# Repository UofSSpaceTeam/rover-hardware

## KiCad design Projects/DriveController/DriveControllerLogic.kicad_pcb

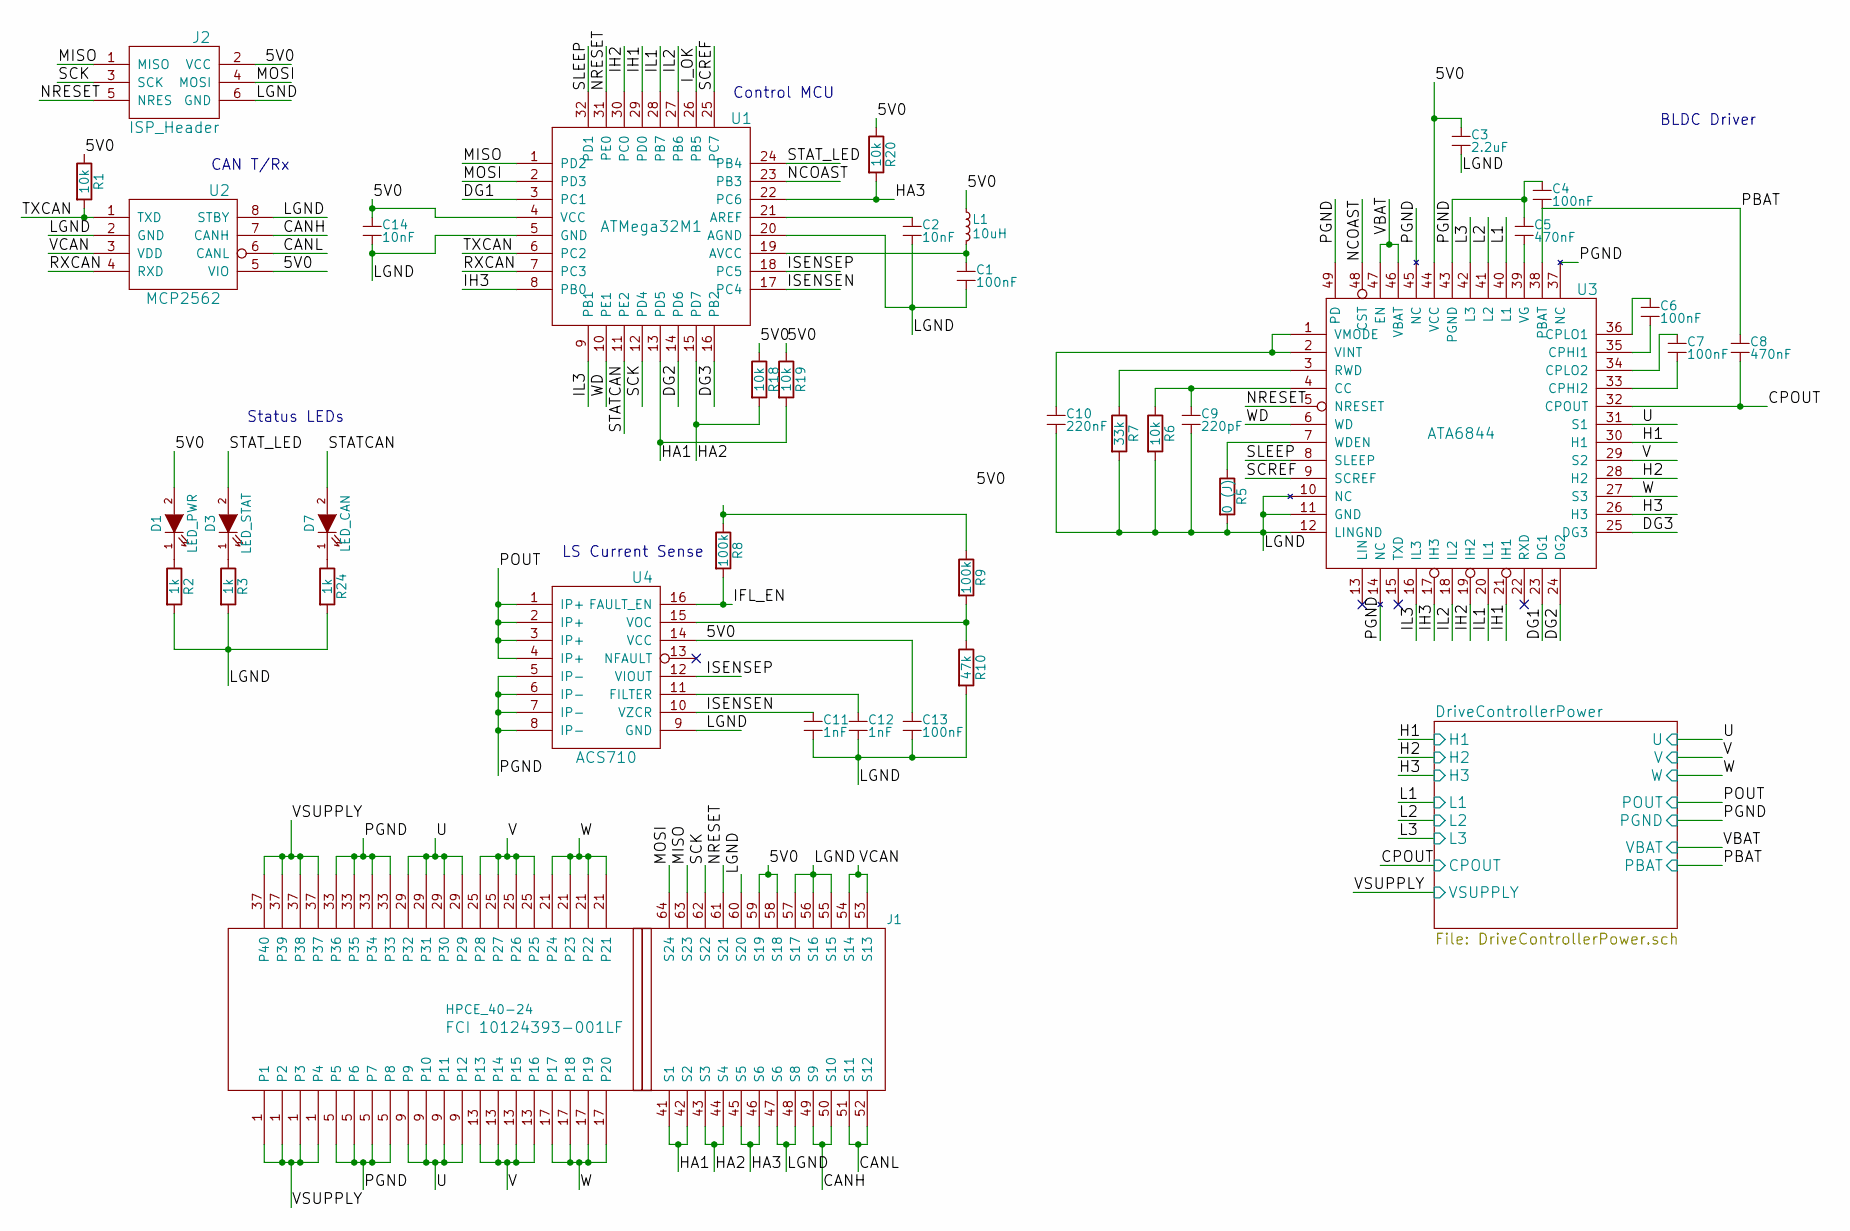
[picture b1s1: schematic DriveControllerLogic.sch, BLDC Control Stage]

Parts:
C1, C4, C6, C7, C13: 100nF; C_0805
C2, C14: 10nF; C_0805
C3: 2.2uF; C_0805
C5, C8: 470nF; C_0805
C9: 220pF; C_0805
C10: 220nF; C_0805
C11, C12: 1nF; C_0805
D1: LED_PWR; LED-0805
D3: LED_STAT; LED-0805
D7: LED_CAN; LED-0805
J1: HPCE_40-24; HPCE-40-24; Part FCI 10124393-001LF
J2: ISP_Header; Pin_Header_Straight_2x03
L1: 10uH; C_0805
R1, R6, R18, R19, R20: 10k; R_0805
R2, R3, R24: 1k; R_0805
R5: 0 (J); R_0805
R7: 33k; R_0805
R8, R9: 100k; R_0805
R10: 47k; R_0805
U1: ATMega32M1; TQFP-32_7x7mm_Pitch0.8mm
U2: MCP2562; SOIC-8_3.9x4.9mm_Pitch1.27mm
U3: ATA6844; QFN-48-1EP_7x7mm_Pitch0.5mm
U4: ACS710; SOIC-16_7.5x10.3mm_Pitch1.27mm

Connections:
/5V0: C3.1, C13.1, C14.1, D1.2 (A), J1.58 (S18), J1.59 (S19), J2.2 (VCC), L1.1, R1.1, R18.1, R19.1, R20.1, U1.4 (VCC), U2.5 (VIO), U3.44 (VCC), U4.14 (VCC)
/CANH: J1.49 (S9), J1.50 (S10), U2.7 (CANH)
/CANL: J1.51 (S11), J1.52 (S12), U2.6 (CANL)
/DG1: U1.3 (PC1), U3.23 (DG1)
/DG2: U1.14 (PD6), U3.24 (DG2)
/DG3: U1.16 (PB2), U3.25 (DG3)
/DriveControllerPower/CPOUT: C8.2, U3.32 (CPOUT); also elsewhere on the board
/DriveControllerPower/H1: U3.30 (H1); also elsewhere on the board
/DriveControllerPower/H2: U3.28 (H2); also elsewhere on the board
/DriveControllerPower/H3: U3.26 (H3); also elsewhere on the board
/DriveControllerPower/L1: U3.40 (L1); also elsewhere on the board
/DriveControllerPower/L2: U3.41 (L2); also elsewhere on the board
/DriveControllerPower/L3: U3.42 (L3); also elsewhere on the board
/DriveControllerPower/PBAT: C4.2, C8.1, U3.38 (PBAT); also elsewhere on the board
/DriveControllerPower/PGND: C4.1, C5.1, J1.5, J1.33, U3.14 (NC), U3.37 (NC), U3.43 (PGND), U3.45 (NC), U3.49 (PD), U4.5 (IP-), U4.6 (IP-), U4.7 (IP-), U4.8 (IP-); also elsewhere on the board
/DriveControllerPower/POUT: U4.1 (IP+), U4.2 (IP+), U4.3 (IP+), U4.4 (IP+); also elsewhere on the board
/DriveControllerPower/U: J1.9 (P10), J1.29, U3.31 (S1); also elsewhere on the board
/DriveControllerPower/V: J1.13, J1.25, U3.29 (S2); also elsewhere on the board
/DriveControllerPower/VBAT: U3.46 (VBAT), U3.47 (EN); also elsewhere on the board
/DriveControllerPower/VSUPPLY: J1.1, J1.37; also elsewhere on the board
/DriveControllerPower/W: J1.17, J1.21, U3.27 (S3); also elsewhere on the board
/HA1: J1.41 (S1), J1.42 (S2), R19.2, U1.13 (PD5)
/HA2: J1.43 (S3), J1.44 (S4), R18.2, U1.15 (PD7)
/HA3: J1.45 (S5), J1.46 (S6), R20.2, U1.22 (PC6)
/IFL_EN: R8.2, U4.16 (FAULT_EN)
/IH1: U1.29 (PD0), U3.21 (IH1)
/IH2: U1.30 (PC0), U3.19 (IH2)
/IH3: U1.8 (PB0), U3.17 (IH3)
/IL1: U1.28 (PB7), U3.20 (IL1)
/IL2: U1.27 (PB6), U3.18 (IL2)
/IL3: U1.9 (PB1), U3.16 (IL3)
/ISENSEN: C11.1, U1.17 (PC4), U4.10 (VZCR)
/ISENSEP: U1.18 (PC5), U4.12 (VIOUT)
/LGND: C1.2, C2.2, C3.2, C9.2, C10.2, C11.2, C12.2, C13.2, C14.2, J1.47 (S6), J1.48 (S8), J1.55 (S15), J1.56 (S16), J1.57 (S17), J1.60 (S20), J2.6 (GND), R2.2, R3.2, R5.2, R6.2, R7.2, R10.2, R24.2, U1.5 (GND), U1.20 (AGND), U2.2 (GND), U2.8 (STBY), U3.10 (NC), U3.11 (GND), U3.12 (LINGND), U4.9 (GND)
/MISO: J1.63 (S23), J2.1 (MISO), U1.1 (PD2)
/MOSI: J1.64 (S24), J2.4 (MOSI), U1.2 (PD3)
/NCOAST: U1.23 (PB3), U3.48 (CST)
/NRESET: J1.61 (S21), J2.5 (NRES), U1.31 (PE0), U3.5 (NRESET)
/RXCAN: U1.7 (PC3), U2.4 (RXD)
/SCK: J1.62 (S22), J2.3 (SCK), U1.12 (PD4)
/SCREF: U1.25 (PC7), U3.9 (SCREF)
/SLEEP: U1.32 (PD1), U3.8 (SLEEP)
/STATCAN: D7.2 (A), U1.11 (PE2)
/STAT_LED: D3.2 (A), U1.24 (PB4)
/TXCAN: R1.2, U1.6 (PC2), U2.1 (TXD)
/VCAN: J1.53 (S13), J1.54 (S14), U2.3 (VDD)
/WD: U1.10 (PE1), U3.6 (WD)
unnamed: C1.1, L1.2, U1.19 (AVCC)
unnamed: C2.1, U1.21 (AREF)
unnamed: C5.2, U3.39 (VG)
unnamed: C6.1, U3.36 (CPLO1)
unnamed: C6.2, U3.35 (CPHI1)
unnamed: C7.1, U3.34 (CPLO2)
unnamed: C7.2, U3.33 (CPHI2)
unnamed: C9.1, R6.1, U3.4 (CC)
unnamed: C10.1, U3.1 (VMODE), U3.2 (VINT)
unnamed: C12.1, U4.11 (FILTER)
unnamed: D1.1 (K), R2.1
unnamed: D3.1 (K), R3.1
unnamed: D7.1 (K), R24.1
unnamed: R5.1, U3.7 (WDEN)
unnamed: R7.1, U3.3 (RWD)
unnamed: R8.1, R9.1
unnamed: R9.2, R10.1, U4.15 (VOC)

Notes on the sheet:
CAN T/Rx
Control MCU
BLDC Driver
LS Current Sense
Status LEDs

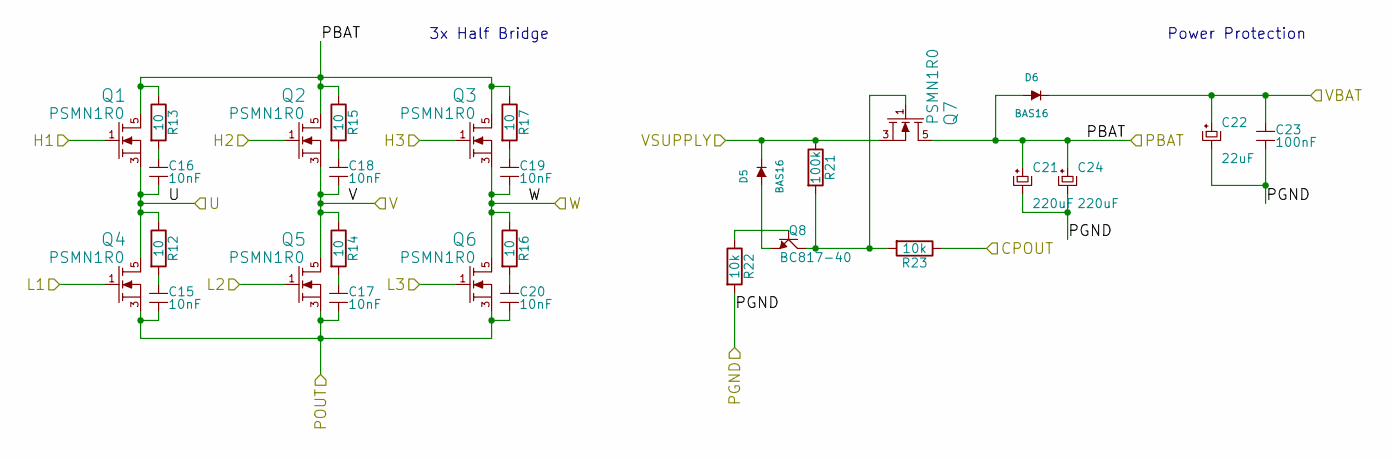
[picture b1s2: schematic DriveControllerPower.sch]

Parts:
C15, C16, C17, C18, C19, C20: 10nF; C_0805
C21, C24: 220uF; c_elec_10x10
C22: 22uF; c_elec_6.3x5.7
C23: 100nF; C_0805
D5, D6: BAS16; SOT-23
Q1, Q2, Q3, Q4, Q5, Q6, Q7: PSMN1R0; SOT-669_LFPAK_POWERSO8
Q8: BC817-40; SOT-23
R12, R13, R14, R15, R16, R17: 10; R_0805
R21: 100k; R_0805
R22, R23: 10k; R_0805

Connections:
/DriveControllerPower/CPOUT: R23.1; also elsewhere on the board
/DriveControllerPower/H1: Q1.1 (G); also elsewhere on the board
/DriveControllerPower/H2: Q2.1 (G); also elsewhere on the board
/DriveControllerPower/H3: Q3.1 (G); also elsewhere on the board
/DriveControllerPower/L1: Q4.1 (G); also elsewhere on the board
/DriveControllerPower/L2: Q5.1 (G); also elsewhere on the board
/DriveControllerPower/L3: Q6.1 (G); also elsewhere on the board
/DriveControllerPower/PBAT: C21.1, C24.1, D6.1 (A), Q1.5 (D), Q2.5 (D), Q3.5 (D), Q7.5 (D), R13.1, R15.1, R17.1; also elsewhere on the board
/DriveControllerPower/PGND: C21.2, C22.2, C23.2, C24.2, R22.2; also elsewhere on the board
/DriveControllerPower/POUT: C15.2, C17.2, C20.2, Q4.3 (S), Q5.3 (S), Q6.3 (S); also elsewhere on the board
/DriveControllerPower/U: C16.2, Q1.3 (S), Q4.5 (D), R12.1; also elsewhere on the board
/DriveControllerPower/V: C18.2, Q2.3 (S), Q5.5 (D), R14.1; also elsewhere on the board
/DriveControllerPower/VBAT: C22.1, C23.1, D6.3 (K); also elsewhere on the board
/DriveControllerPower/VSUPPLY: D5.3 (K), Q7.3 (S), R21.1; also elsewhere on the board
/DriveControllerPower/W: C19.2, Q3.3 (S), Q6.5 (D), R16.1; also elsewhere on the board
unnamed: C15.1, R12.2
unnamed: C16.1, R13.2
unnamed: C17.1, R14.2
unnamed: C18.1, R15.2
unnamed: C19.1, R17.2
unnamed: C20.1, R16.2
unnamed: D5.1 (A), Q8.2 (E)
unnamed: Q7.1 (G), Q8.3 (C), R21.2, R23.2
unnamed: Q8.1 (B), R22.1

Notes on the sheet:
3x Half Bridge
Power Protection

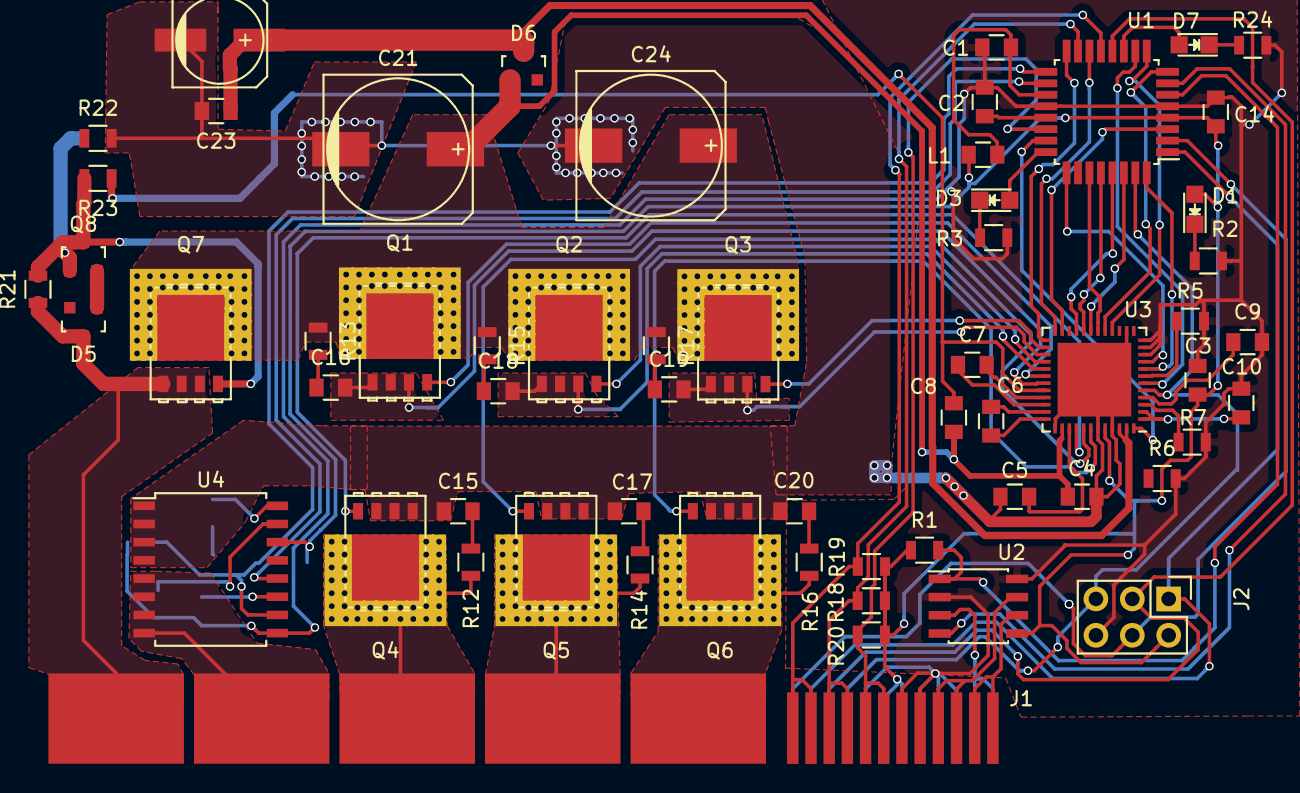
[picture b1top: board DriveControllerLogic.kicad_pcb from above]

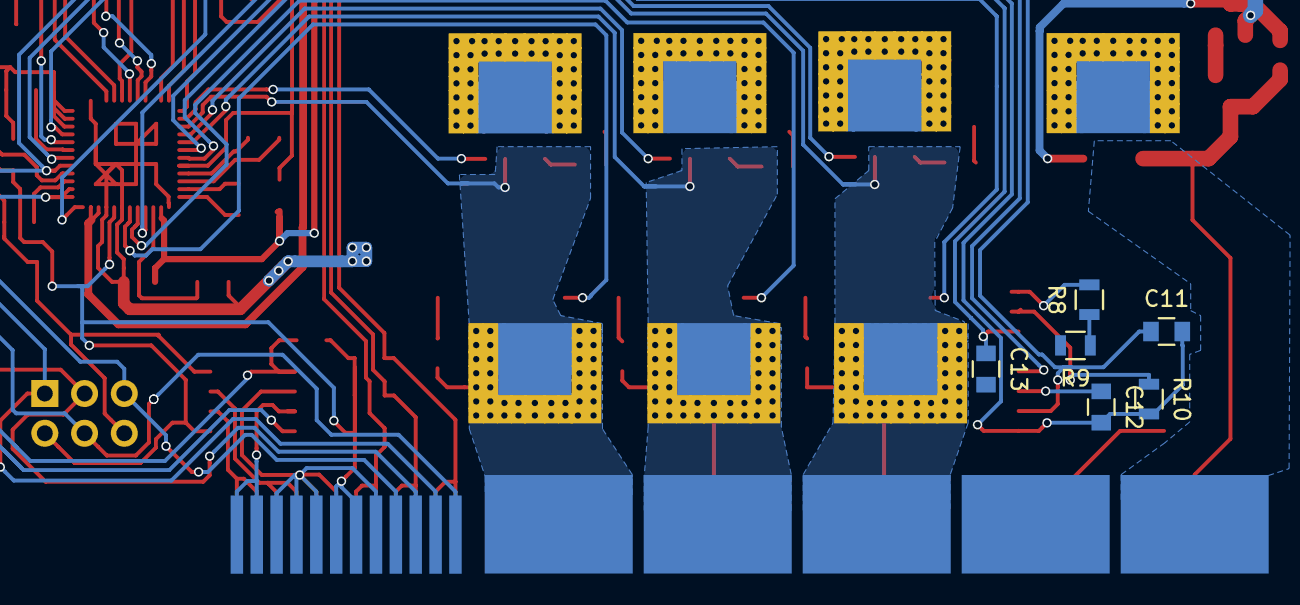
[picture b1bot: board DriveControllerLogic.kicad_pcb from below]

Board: 2 copper layers, 66 parts (6 on the bottom side), 73 nets.

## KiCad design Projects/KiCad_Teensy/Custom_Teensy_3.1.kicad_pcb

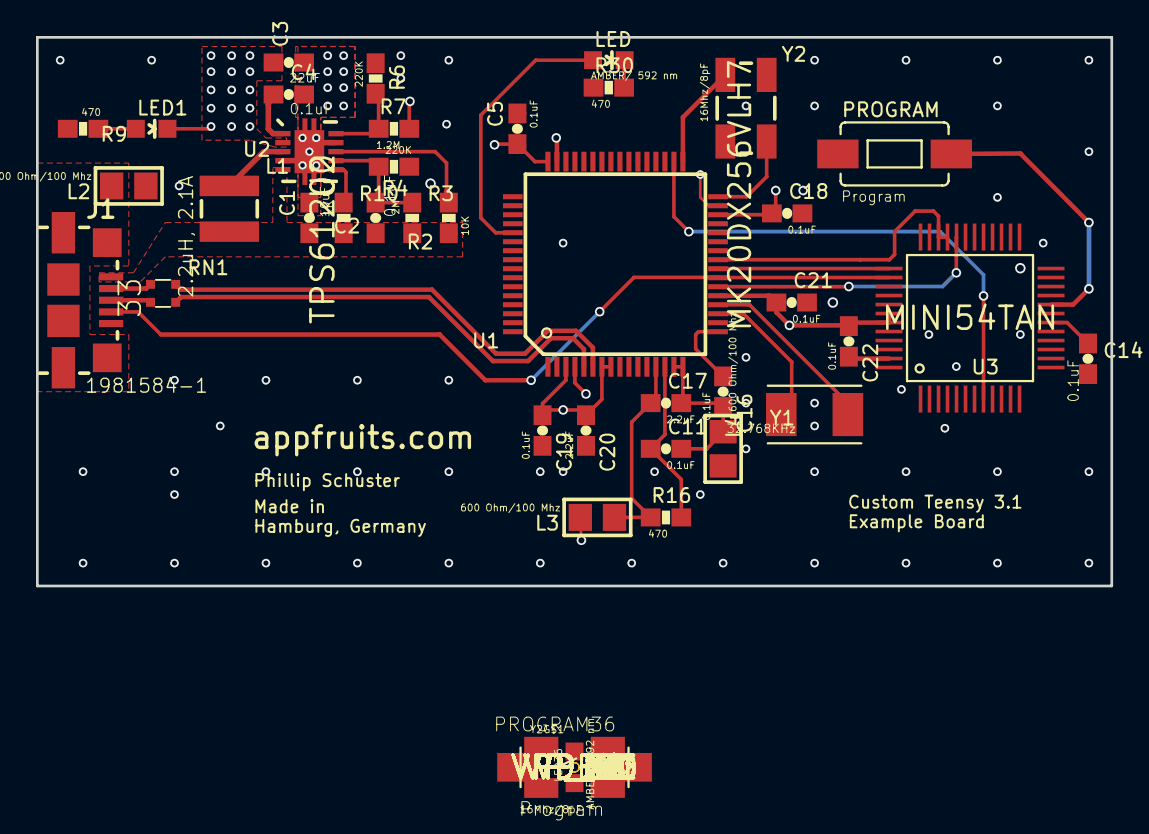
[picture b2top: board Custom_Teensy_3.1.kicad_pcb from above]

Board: 4 copper layers, 59.7 x 30.5 mm, 130 parts (0 on the bottom side), 32 nets.

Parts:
C1: 10uF; 0603-CAP
C2, C4, C5, C11, C14, C16, C18, C19, C21, C22: 0.1uF; 0603-CAP
C3: 22uF; 0603-CAP
C17, C20: 2.2uF; 0603-CAP
J1: 1981584-1
L1: 2.2uH, 2.1A; LPS3015
L2, L3, L4: 600 Ohm/100 Mhz; 0805
LED: AMBER/ 592 nm; LED-0603
LED1: LED-0603
LED36: AMBER/ 592 nm; APPFRUITS_LED-0603
PROGRAM: Program; TACTILE-SWITCH-1101NE
PROGRAM36: Program; SPARKFUN-ELECTROMECHANICAL_TACTILE-SWITCH-1101NE
R2: 10K; 0603-RES
R3: 2M; 0603-RES
R4, R6: 220K; 0603-RES
R7: 1.2M; 0603-RES
R9, R16, R30: 470; 0603-RES
R10: 1K; 0603-RES
RN1: 33; EXB34V
U1: MK20DX256VLH7
U2: TPS61200; QFN-10_PAD
U3: MINI54TAN
VP_0, VP_1, VP_2, VP_3, VP_4, VP_5, VP_6, VP_7, VP_8, VP_9, VP_10, VP_11, VP_12, VP_13, VP_23, VP_24, VP_25, VP_26, VP_27, VP_28, VP_29, VP_30, VP_31, VP_32, VP_33, VP_34, VP_35, VP_36, VP_37, VP_38, VP_39, VP_40, VP_41, VP_42, VP_43, VP_44, VP_45, VP_46, VP_47, VP_48, VP_49, VP_50, VP_51, VP_52, VP_53, VP_54, VP_55, VP_56, VP_57, VP_58, VP_59, VP_60, VP_61, VP_62, VP_63, VP_64, VP_65, VP_66, VP_67, VP_68, VP_69, VP_70, VP_71, VP_72, VP_73, VP_74, VP_75, VP_76, VP_77, VP_78, VP_79, VP_80, VP_81, VP_82, VP_83, VP_84, VP_85, VP_86, VP_87, VP_88, VP_89: VPDEV0; VPAD_VPAC0
VP_14, VP_15, VP_16: VPDEV1; VPAD_VPAC1
VP_17: VPDEV2; VPAD_VPAC2
VP_18, VP_19, VP_20, VP_21, VP_22: VPDEV3; VPAD_VPAC3
Y1: 32.768KHz; CRYSTAL-TXC-7A
Y2: 16Mhz/8pF; CRYSTAL-SMD-5X3
Y2G$1: 16Mhz/8pF; APPFRUITS_CRYSTAL-SMD-5X3

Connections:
3.3V: C3.1, C5.1, C18.1, C19.1, C20.1, C21.1, C22.1, L3.2, LED1.C, R7.2, U1.3, U1.7, U1.8, U1.21, U1.30, U1.48, U2.2, U3.42, U3.43, VP_0.VP, VP_1.VP, VP_2.VP, VP_3.VP, VP_4.VP, VP_5.VP, VP_6.VP, VP_7.VP, VP_8.VP, VP_9.VP, VP_10.VP, VP_11.VP, VP_12.VP, VP_13.VP
/FB: R6.2, R7.1, U2.10
/ID: J1.4, U1.23, U3.38
/N$1: LED1.A, R9.1
/N$2: L1.1, U2.3
/N$12: LED36.A, U1.53
/N$15: U1.24, U3.37
/N$18: LED36.C, R30.2
/N$19: PROGRAM36.P$2, U3.20
/N$22: C14.1, U3.18
/N$27: U1.32, Y2G$1.3
/N$28: U1.33, Y2G$1.1
/N$29: U1.19, Y1.P$2
/N$30: U1.20, Y1.P$1
/PS: R2.2, U2.8
/RESET_B: U1.34, U3.8
/SOFTPOWER: R10.1, U2.6
/SWD_CLK: U1.22, U3.32
/SWD_DIO: U1.25, U3.33, U3.34
/USB_CON_N: J1.2, RN1.1
/USB_CON_P: J1.3, RN1.2
/USB_D_N: RN1.4, U1.6
/USB_D_P: RN1.3, U1.5
/UVLO: C2.2, R3.1, R4.2, U2.7
/VAUX: C4.1, U2.1
/VDDA: C17.1, L3.1, R16.1, U1.13
/VREFH: C11.1, R16.2, U1.14
/VREFL: C11.2, C16.2, C17.2, L4.2, U1.15, U1.16
/VREF_OUT: C16.1, U1.17
GND: C1.2, C3.2, C4.2, C5.2, C14.2, C18.2, C19.2, C20.2, C21.2, C22.2, J1.5, L2.1, L4.1, PROGRAM.P$1, PROGRAM36.P$1, R4.1, R6.1, R9.2, R30.1, U1.4, U1.31, U1.47, U2.4, U2.9, U2.11, U2.12, U2.13, U2.14, U2.15, U3.5, U3.17, U3.25, U3.47, VP_14.VP, VP_15.VP, VP_16.VP, VP_17.VP, VP_18.VP, VP_19.VP, VP_20.VP, VP_21.VP, VP_22.VP, VP_23.VP, VP_24.VP, VP_25.VP, VP_26.VP, VP_27.VP, VP_28.VP, VP_29.VP, VP_30.VP, VP_31.VP, VP_32.VP, VP_33.VP, VP_34.VP, VP_35.VP, VP_36.VP, VP_37.VP, VP_38.VP, VP_39.VP, VP_40.VP, VP_41.VP, VP_42.VP, VP_43.VP, VP_44.VP, VP_45.VP, VP_46.VP, VP_47.VP, VP_48.VP, VP_49.VP, VP_50.VP, VP_51.VP, VP_52.VP, VP_53.VP, VP_54.VP, VP_55.VP, VP_56.VP, VP_57.VP, VP_58.VP, VP_59.VP, VP_60.VP, VP_61.VP, VP_62.VP, VP_63.VP, VP_64.VP, VP_65.VP, VP_66.VP, VP_67.VP, VP_68.VP, VP_69.VP, VP_70.VP, VP_71.VP, VP_72.VP, VP_73.VP, VP_74.VP, VP_75.VP, VP_76.VP, VP_77.VP, VP_78.VP, VP_79.VP, VP_80.VP, VP_81.VP, VP_82.VP, VP_83.VP, VP_84.VP, VP_85.VP, VP_86.VP, VP_87.VP, VP_88.VP, VP_89.VP
USB_SHIELD: J1.S1, J1.S2, J1.S3, J1.S4, L2.2
VCC: C1.1, C2.1, J1.1, L1.2, R2.1, R3.2, R10.2, U2.5

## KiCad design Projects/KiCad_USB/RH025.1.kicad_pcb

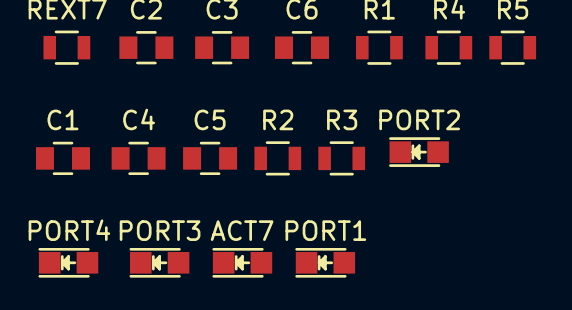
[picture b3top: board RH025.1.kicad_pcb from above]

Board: 2 copper layers, 17 parts (0 on the bottom side), 5 nets, no tracks yet.

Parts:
ACT7: LED_0805
C1, C3, C6: 0.1uF; C_0805
C2, C4, C5: 10uF; C_0805
PORT1, PORT2, PORT3, PORT4: LED_0805
R1: 100K; R_0805
R2: 47K; R_0805
R3, R4, R5: 330; R_0805
REXT7: 2.7K; R_0805

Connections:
3V3: C1.1, C2.1
/N$8: C3.1, C4.1
/N$13: R1.2, R2.1
GND: C1.2, C2.2, C3.2, C4.2, C5.2, C6.2, R1.1, R5.1, REXT7.1
VBUS: C5.1, C6.1, R2.2

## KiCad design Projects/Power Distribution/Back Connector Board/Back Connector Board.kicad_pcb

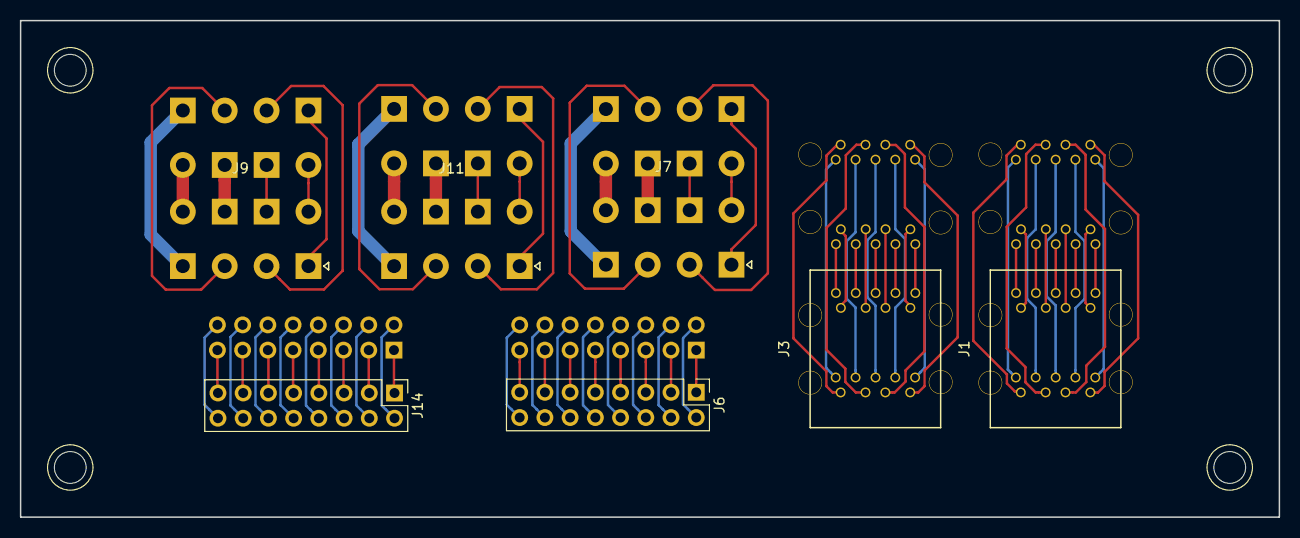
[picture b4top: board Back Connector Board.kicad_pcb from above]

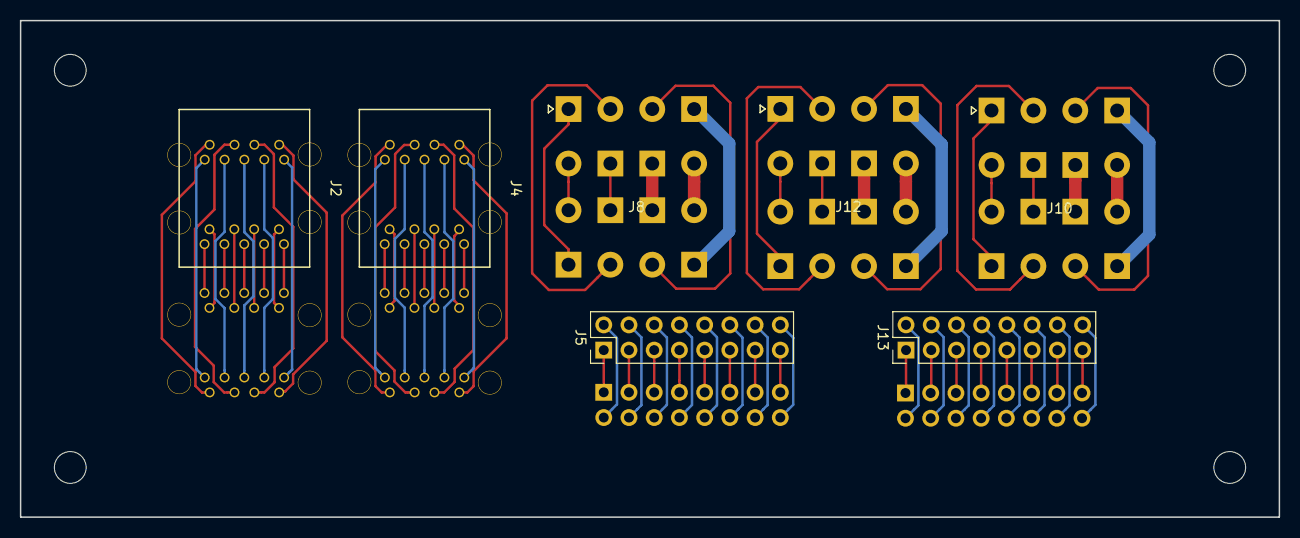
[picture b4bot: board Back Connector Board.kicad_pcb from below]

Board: 2 copper layers, 126.8 x 50.0 mm, 14 parts (7 on the bottom side), 92 nets.

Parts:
J1, J2, J3, J4: Conn_02x09_Odd_Even; USBA_3.0_Stacked_Vertical-Molex_48409
J5, J6, J13, J14: Conn_02x08_Odd_Even; Pin_Header_Straight_2x08_Pitch2.54mm
J7, J8, J9, J10, J11, J12: Molex_MiniFit_02x04; Molex_MiniFit-JR_5566-08A_02x04x4.2_Vertical

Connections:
unnamed: J1.1, J2.1
unnamed: J1.2, J2.2
unnamed: J1.3, J2.3
unnamed: J1.4, J2.4
unnamed: J1.5, J2.5
unnamed: J1.6, J2.6
unnamed: J1.7, J2.7
unnamed: J1.8, J2.8
unnamed: J1.9, J2.9
unnamed: J1.10, J2.10
unnamed: J1.11, J2.11
unnamed: J1.12, J2.12
unnamed: J1.13, J2.13
unnamed: J1.14, J2.14
unnamed: J1.15, J2.15
unnamed: J1.16, J2.16
unnamed: J1.17, J2.17
unnamed: J1.18, J2.18
unnamed: J3.1, J4.1
unnamed: J3.2, J4.2
unnamed: J3.3, J4.3
unnamed: J3.4, J4.4
unnamed: J3.5, J4.5
unnamed: J3.6, J4.6
unnamed: J3.7, J4.7
unnamed: J3.8, J4.8
unnamed: J3.9, J4.9
unnamed: J3.10, J4.10
unnamed: J3.11, J4.11
unnamed: J3.12, J4.12
unnamed: J3.13, J4.13
unnamed: J3.14, J4.14
unnamed: J3.15, J4.15
unnamed: J3.16, J4.16
unnamed: J3.17, J4.17
unnamed: J3.18, J4.18
unnamed: J5.1, J6.1
unnamed: J5.2, J6.2
unnamed: J5.3, J6.3
unnamed: J5.4, J6.4
unnamed: J5.5, J6.5
unnamed: J5.6, J6.6
unnamed: J5.7, J6.7
unnamed: J5.8, J6.8
unnamed: J5.9, J6.9
unnamed: J5.10, J6.10
unnamed: J5.11, J6.11
unnamed: J5.12, J6.12
unnamed: J5.13, J6.13
unnamed: J5.14, J6.14
unnamed: J5.15, J6.15
unnamed: J5.16, J6.16
unnamed: J7.1, J8.1
unnamed: J7.2, J8.2
unnamed: J7.3, J8.3
unnamed: J7.4, J8.4
unnamed: J7.5, J8.5
unnamed: J7.6, J8.6
unnamed: J7.7, J8.7
unnamed: J7.8, J8.8
unnamed: J9.1, J10.1
unnamed: J9.2, J10.2
unnamed: J9.3, J10.3
unnamed: J9.4, J10.4
unnamed: J9.5, J10.5
unnamed: J9.6, J10.6
unnamed: J9.7, J10.7
unnamed: J9.8, J10.8
unnamed: J11.1, J12.1
unnamed: J11.2, J12.2
unnamed: J11.3, J12.3
unnamed: J11.4, J12.4
unnamed: J11.5, J12.5
unnamed: J11.6, J12.6
unnamed: J11.7, J12.7
unnamed: J11.8, J12.8
unnamed: J13.1, J14.1
unnamed: J13.2, J14.2
unnamed: J13.3, J14.3
unnamed: J13.4, J14.4
unnamed: J13.5, J14.5
unnamed: J13.6, J14.6
unnamed: J13.7, J14.7
unnamed: J13.8, J14.8
unnamed: J13.9, J14.9
unnamed: J13.10, J14.10
unnamed: J13.11, J14.11
unnamed: J13.12, J14.12
unnamed: J13.13, J14.13
unnamed: J13.14, J14.14
unnamed: J13.15, J14.15
unnamed: J13.16, J14.16

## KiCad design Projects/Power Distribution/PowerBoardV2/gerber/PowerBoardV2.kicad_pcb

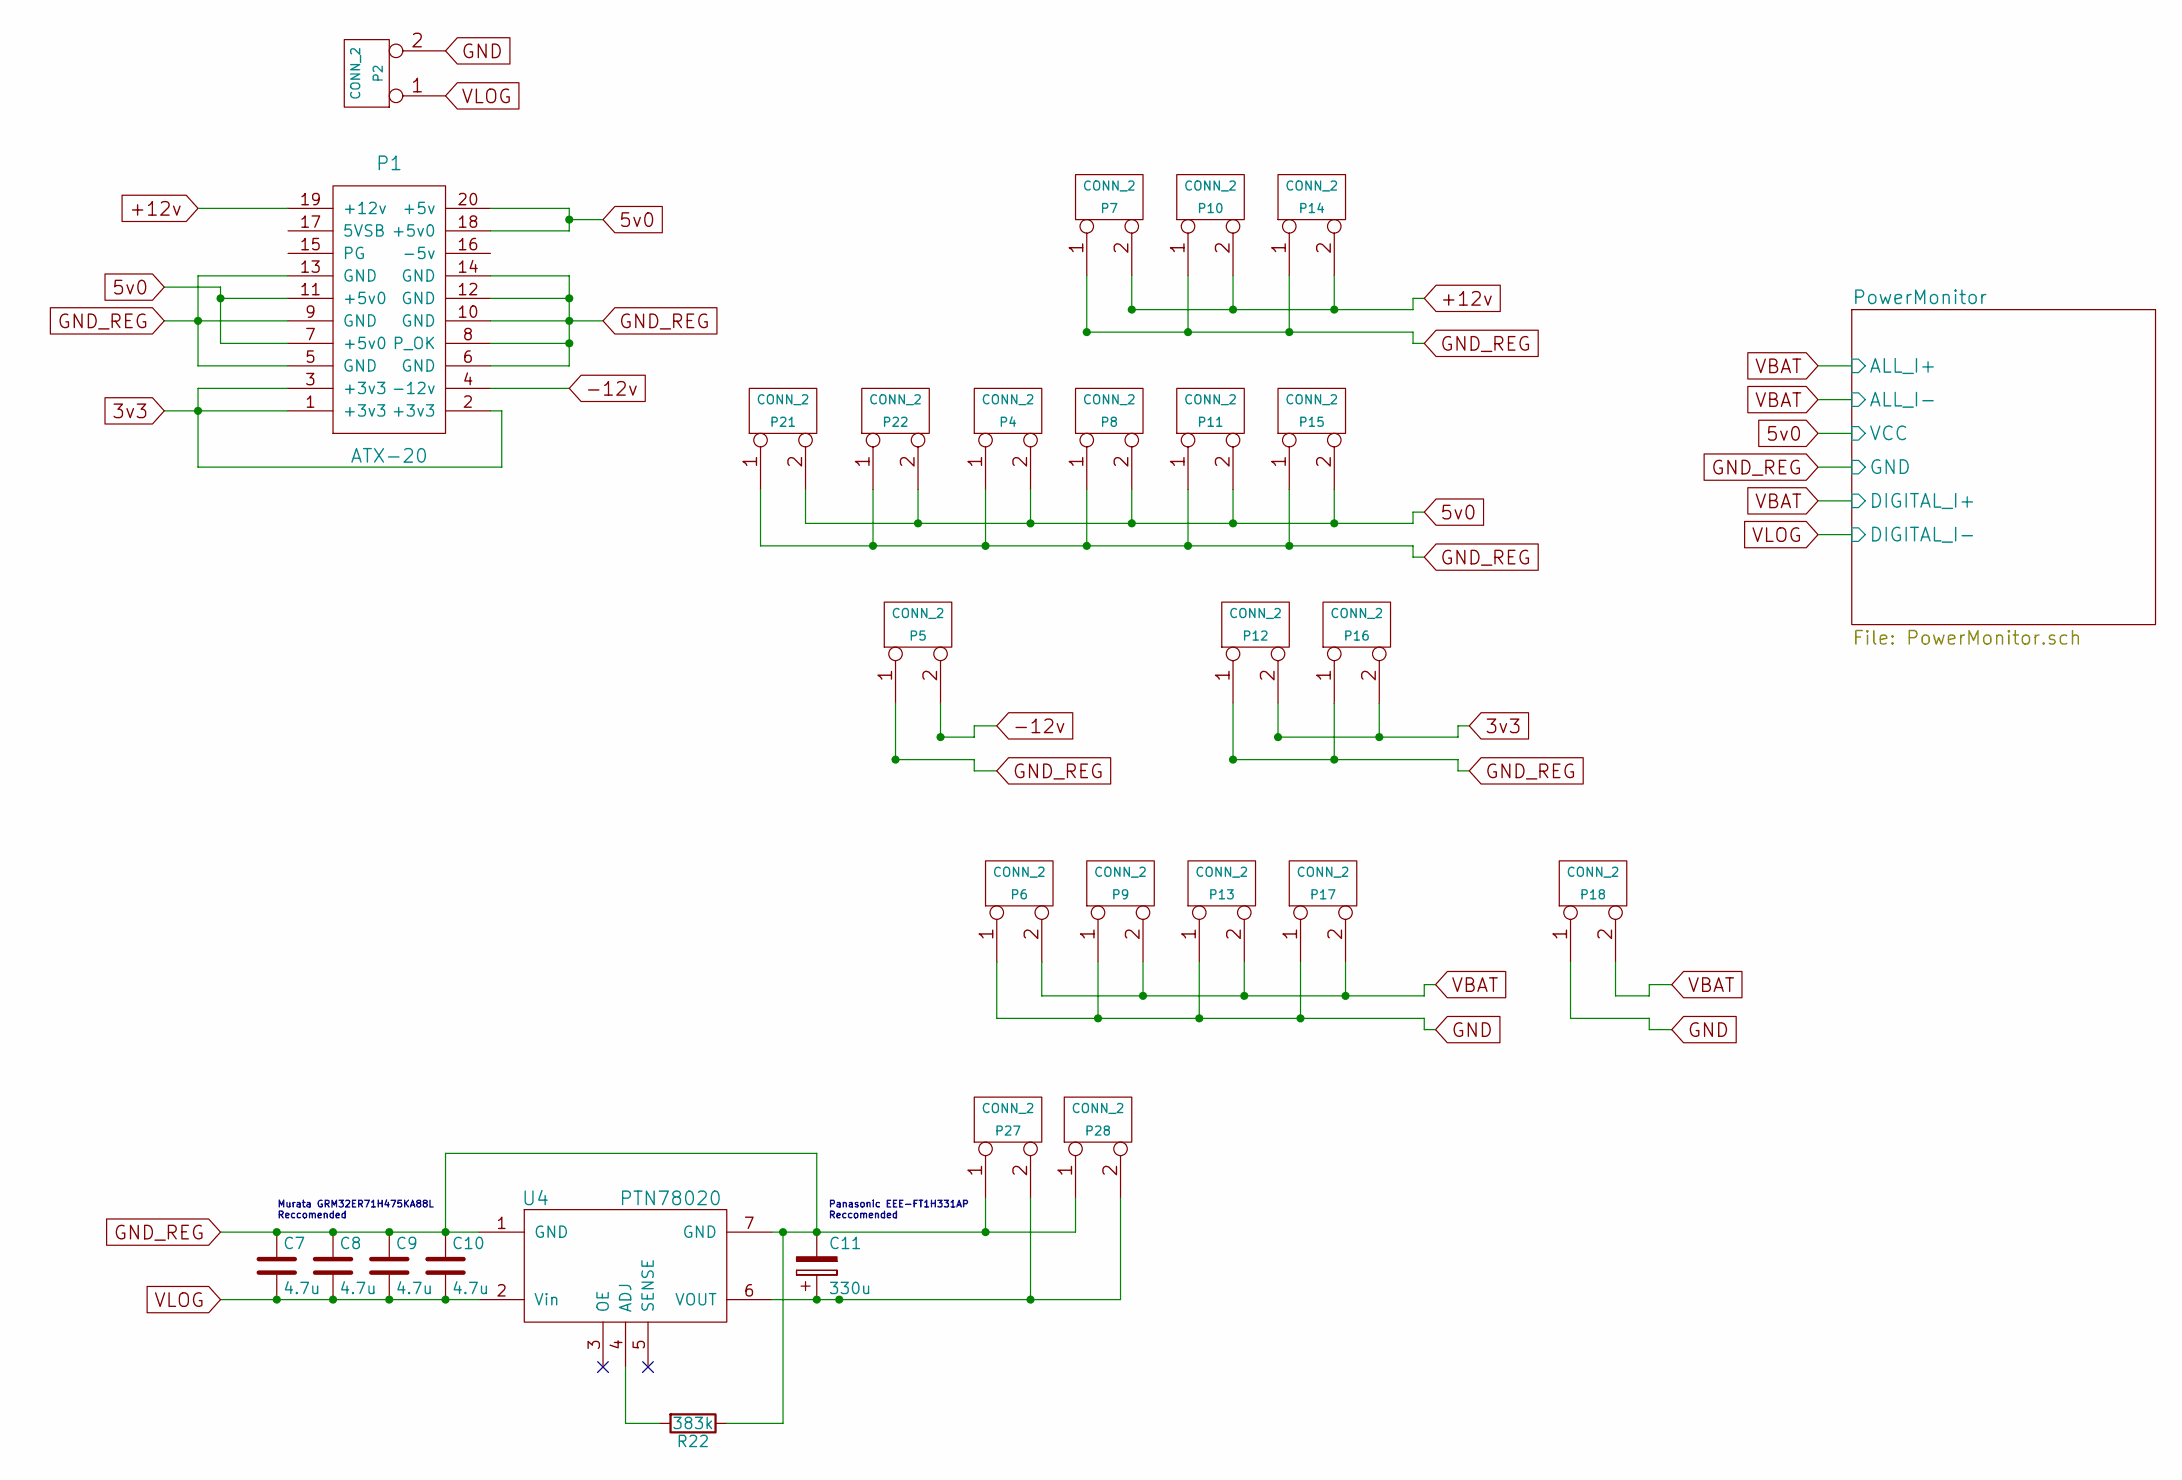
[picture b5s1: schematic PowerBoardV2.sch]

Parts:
C7, C8, C9, C10: 4.7u; C_1210; MPN GRM32ER71H475KA88L
C11: 330u; CP_Elec_10x10.5; MPN EEE-FT1H331AP
P1: ATX-20; ATX20
P2, P4, P5, P7, P8, P10, P11, P12, P14, P15, P16, P21, P22, P27, P28: CONN_2; Molex_39531_1002; MPN 0395311002
P6, P9, P13, P17, P18: CONN_2; Phoenix_Contact_1770539; MPN 1770539
R22: 383k; R_0805; MPN RC0805FR-07383KL
U4: PTN78020; PTN7820H

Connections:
3v3: P1.1 (+3v3), P1.2 (+3v3), P1.3 (+3v3), P12.2 (PM), P16.2 (PM)
5v0: P1.7 (+5v0), P1.11 (+5v0), P1.18 (+5v0), P1.20 (+5v), P4.2 (PM), P8.2 (PM), P11.2 (PM), P15.2 (PM), P21.2 (PM), P22.2 (PM); also elsewhere on the board
+12v: P1.19 (+12v), P7.2 (PM), P10.2 (PM), P14.2 (PM)
-12v: P1.4 (-12v), P5.2 (PM)
GND: P2.2 (PM), P6.1, P9.1, P13.1, P17.1, P18.1
GND_REG: C7.1, C8.1, C9.1, C10.1, C11.2, P1.5 (GND), P1.6 (GND), P1.8 (P_OK), P1.9 (GND), P1.10 (GND), P1.12 (GND), P1.13 (GND), P1.14 (GND), P4.1, P5.1, P7.1, P8.1, P10.1, P11.1, P12.1, P14.1, P15.1, P16.1, P21.1, P22.1, P27.1, P28.1, R22.1, U4.1 (GND), U4.7 (GND); also elsewhere on the board
unnamed: C11.1, P27.2 (PM), P28.2 (PM), U4.6 (VOUT)
unnamed: R22.2, U4.4 (ADJ)
VBAT: P6.2 (PM), P9.2 (PM), P13.2 (PM), P17.2 (PM), P18.2 (PM); also elsewhere on the board
VLOG: C7.2, C8.2, C9.2, C10.2, P2.1, U4.2 (Vin); also elsewhere on the board

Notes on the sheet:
Panasonic EEE-FT1H331AP Reccomended
Murata GRM32ER71H475KA88L Reccomended

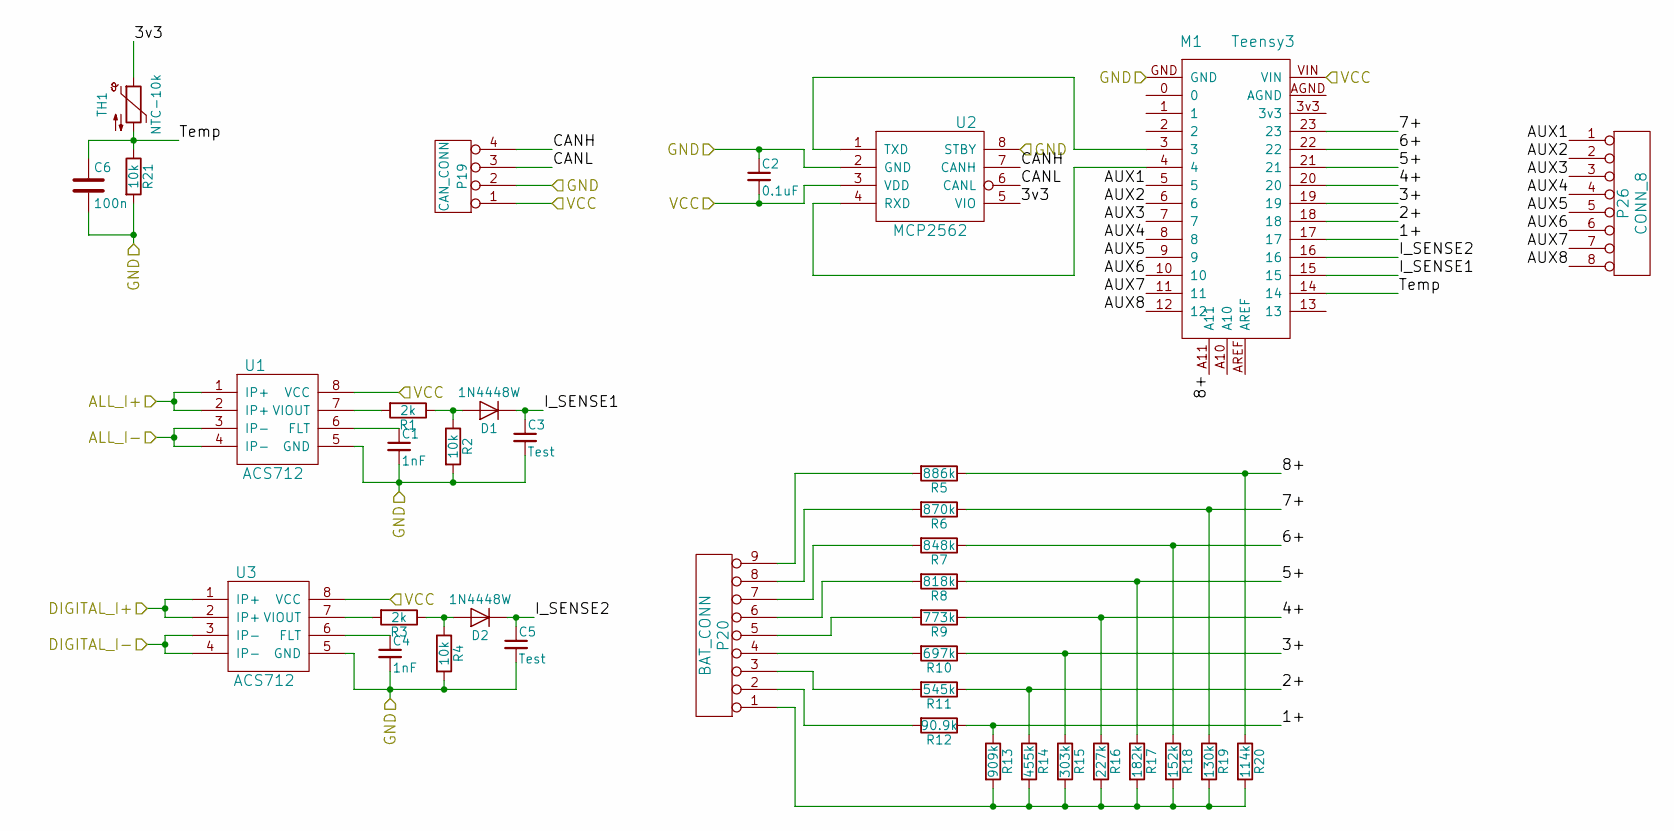
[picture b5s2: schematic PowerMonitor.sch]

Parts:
C1: 1nF; C_1210; MPN C1210C102KGRACTU
C2: 0.1uF; C_1210; MPN C1210C104K1RACTU
C3, C5: Test; C_1210; MPN GRM32QR73A103KW01L
C4: 1nF; C_0805; MPN C0805C102K5RACTU
C6: 100n; C_0805_HandSoldering; MPN 08055C104KAT2A
D1, D2: 1N4448W; D_SOD-123; MPN 1N4448W-TP
M1: Teensy3; Teensy_3.2_NoTail
P19: CAN_CONN; Molex_39502_1004R; MPN 0395021004
P20: BAT_CONN; Molex_39502_1009R; MPN 39502-1009
P26: CONN_8; Socket_Strip_Straight_1x08_Pitch2.54mm; MPN PRPC016SAAN-RC
R1, R3: 2k; R_0805_HandSoldering; MPN RC0805FR-072KL
R2, R4, R21: 10k; R_0805_HandSoldering; MPN RC0805FR-0710KL
R5: 886k; R_0805_HandSoldering; MPN RC0805FR-07887KL
R6: 870k; R_0805_HandSoldering; MPN RC0805FR-07866KL
R7: 848k; R_0805_HandSoldering; MPN RC0805FR-07845KL
R8: 818k; R_0805_HandSoldering; MPN RC0805FR-07820KL
R9: 773k; R_0805_HandSoldering; MPN RC0805FR-07768KL
R10: 697k; R_0805_HandSoldering; MPN RC0805FR-07698KL
R11: 545k; R_0805_HandSoldering; MPN RC0805FR-07549KL
R12: 90.9k; R_0805_HandSoldering; MPN RC0805FR-0790K9L
R13: 909k; R_0805_HandSoldering; MPN RC0805FR-07909KL
R14: 455k; R_0805_HandSoldering; MPN RC0805FR-07453KL
R15: 303k; R_0805_HandSoldering; MPN RC0805FR-07301KL
R16: 227k; R_0805_HandSoldering; MPN RC0805FR-07226KL
R17: 182k; R_0805_HandSoldering; MPN RC0805FR-07182KL
R18: 152k; R_0805_HandSoldering; MPN RC0805FR-07154KL
R19: 130k; R_0805_HandSoldering; MPN RC0805FR-07130KL
R20: 114k; R_0805_HandSoldering; MPN RC0805FR-07115RL
TH1: NTC-10k; R_0805_HandSoldering; MPN NCP18XH103F03RB
U1, U3: ACS712; SOIC-8_3.9x4.9mm_Pitch1.27mm; MPN ACS712ELCTR-20A-T
U2: MCP2562; SOIC-8_3.9x4.9mm_Pitch1.27mm; MPN MCP2562T-E/SN

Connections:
5v0: C2.2, M1.VIN, P19.1, U1.8 (VCC), U2.3 (VDD), U3.8 (VCC); also elsewhere on the board
/PowerMonitor/1+: M1.17, R12.1, R13.1
/PowerMonitor/2+: M1.18, R11.1, R14.1
/PowerMonitor/3+: M1.19, R10.1, R15.1
/PowerMonitor/3v3: TH1.1, U2.5 (VIO)
/PowerMonitor/4+: M1.20, R9.1, R16.1
/PowerMonitor/5+: M1.21, R8.1, R17.1
/PowerMonitor/6+: M1.22, R7.1, R18.1
/PowerMonitor/7+: M1.23, R6.1, R19.1
/PowerMonitor/8+: M1.A11, R5.1, R20.1
/PowerMonitor/AUX1: M1.5, P26.1
/PowerMonitor/AUX2: M1.6, P26.2
/PowerMonitor/AUX3: M1.7, P26.3
/PowerMonitor/AUX4: M1.8, P26.4
/PowerMonitor/AUX5: M1.9, P26.5
/PowerMonitor/AUX6: M1.10, P26.6
/PowerMonitor/AUX7: M1.11, P26.7
/PowerMonitor/AUX8: M1.12, P26.8
/PowerMonitor/CANH: P19.4, U2.7 (CANH)
/PowerMonitor/CANL: P19.3, U2.6 (CANL)
/PowerMonitor/I_SENSE1: C3.1, D1.1 (K), M1.15
/PowerMonitor/I_SENSE2: C5.1, D2.1 (K), M1.16
/PowerMonitor/Temp: C6.1, M1.14, R21.1, TH1.2
GND_REG: C1.2, C2.1, C3.2, C4.2, C5.2, C6.2, M1.GND, P19.2, R2.2, R4.2, R21.2, U1.5 (GND), U2.2 (GND), U2.8 (STBY), U3.5 (GND); also elsewhere on the board
unnamed: C1.1, U1.6 (FLT)
unnamed: C4.1, U3.6 (FLT)
unnamed: D1.2 (A), R1.1, R2.1
unnamed: D2.2 (A), R3.1, R4.1
unnamed: M1.3, U2.1 (TXD)
unnamed: M1.4, U2.4 (RXD)
unnamed: P20.1, R13.2, R14.2, R15.2, R16.2, R17.2, R18.2, R19.2, R20.2
unnamed: P20.2, R12.2
unnamed: P20.3, R11.2
unnamed: P20.4, R10.2
unnamed: P20.5, R9.2
unnamed: P20.6, R8.2
unnamed: P20.7, R7.2
unnamed: P20.8, R6.2
unnamed: P20.9, R5.2
unnamed: R1.2, U1.7 (VIOUT)
unnamed: R3.2, U3.7 (VIOUT)
VBAT: U1.1 (IP+), U1.2 (IP+), U1.3 (IP-), U1.4 (IP-), U3.1 (IP+), U3.2 (IP+); also elsewhere on the board
VLOG: U3.3 (IP-), U3.4 (IP-); also elsewhere on the board

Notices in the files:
Projects/KiCad_Teensy/Custom_Teensy_3.1.kicad_pcb:
Released under the Creative Commons Attribution Share-Alike 4.0 License
https://creativecommons.org/licenses/by-sa/4.0
to use/see all necessary layers. EAGLEs hobbyist license will do the trick.
